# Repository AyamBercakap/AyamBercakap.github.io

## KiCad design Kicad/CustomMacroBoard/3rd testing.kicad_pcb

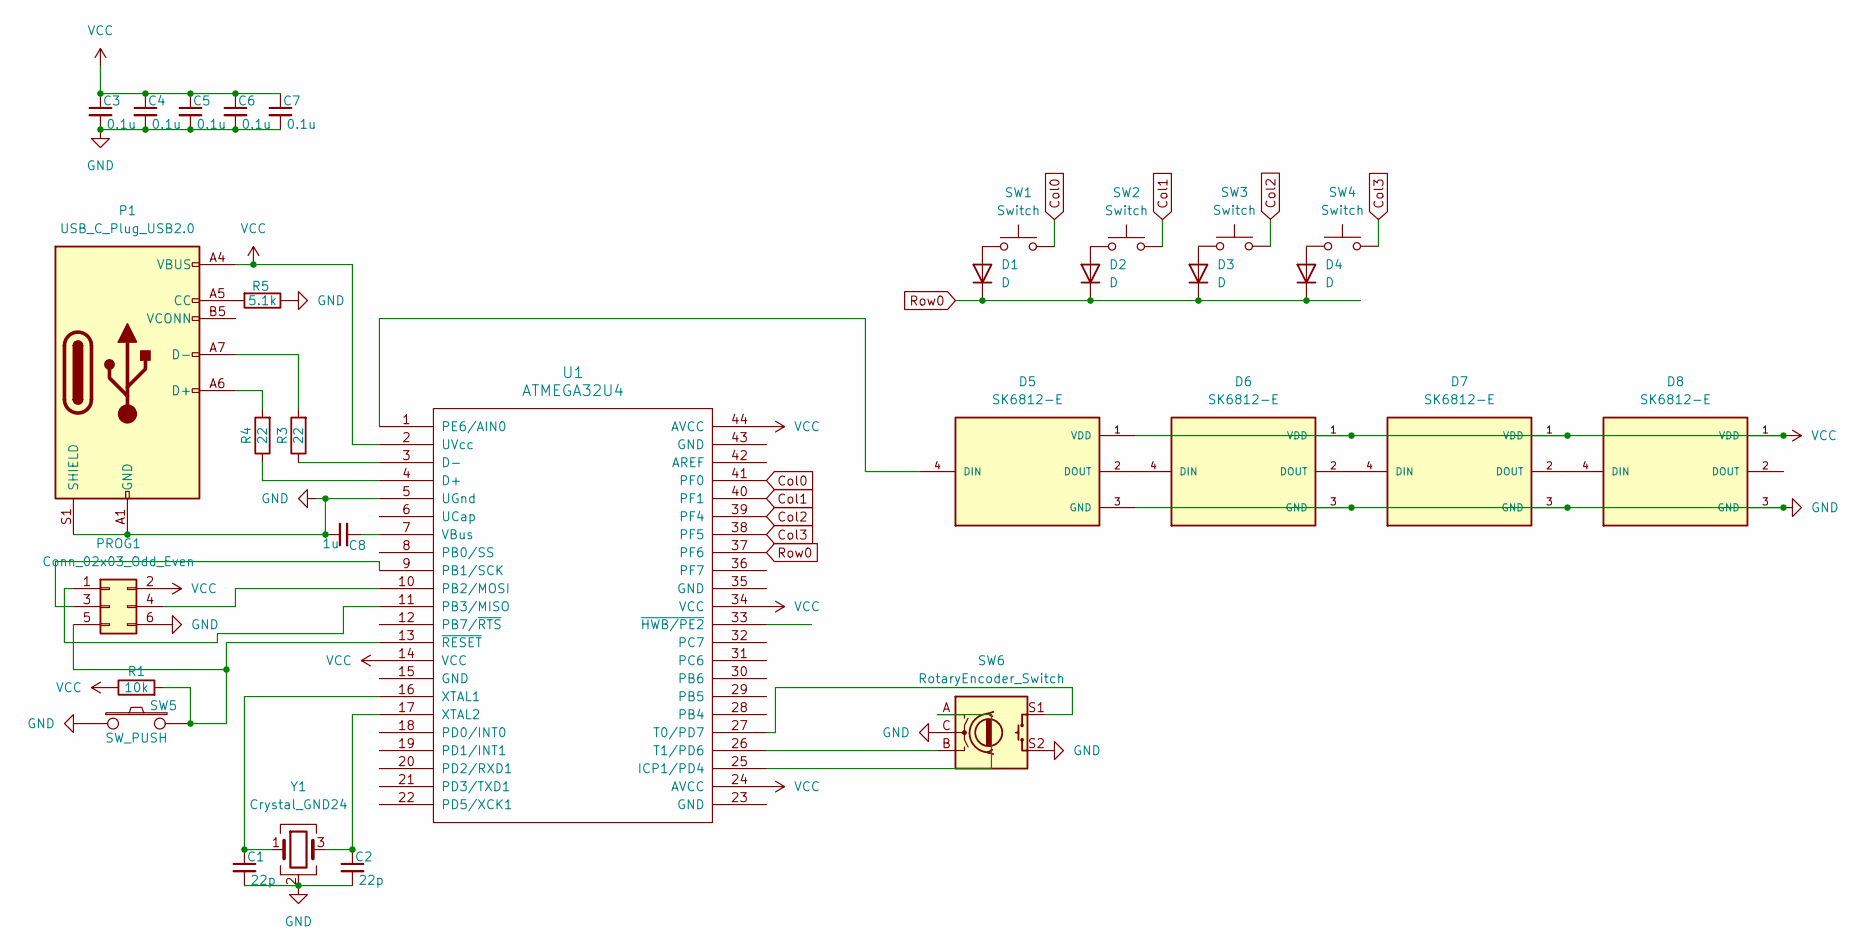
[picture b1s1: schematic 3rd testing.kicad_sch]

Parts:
C1, C2: 22p; C_0805_2012Metric_Pad1.18x1.45mm_HandSolder
C3, C4, C5, C6, C7: 0.1u; C_0805_2012Metric_Pad1.18x1.45mm_HandSolder
C8: 1u; C_0805_2012Metric_Pad1.18x1.45mm_HandSolder
D1, D2, D3, D4: D; D_SOD123_axial
D5, D6, D7, D8: SK6812-E; LED_SK6812-E; PARTREV 2
P1: USB_C_Plug_USB2.0; USB_C_Receptacle_GCT_USB4085
PROG1: Conn_02x03_Odd_Even; pads
R1: 10k; R_0805_2012Metric_Pad1.20x1.40mm_HandSolder
R3, R4: 22; R_0805_2012Metric_Pad1.20x1.40mm_HandSolder
R5: 5.1k; R_0805_2012Metric_Pad1.20x1.40mm_HandSolder
SW1, SW2, SW3, SW4: Switch; MX_PCB_1.00u
SW5: SW_PUSH; SW_SPST_TL3342
SW6: RotaryEncoder_Switch; RotaryEncoder_Alps_EC11E-Switch_Vertical_H20mm
U1: ATMEGA32U4; TQFN-44-1EP_7x7mm_P0.5mm_EP4.7x4.7mm
Y1: Crystal_GND24; Crystal_SMD_SeikoEpson_FA238-4Pin_3.2x2.5mm_HandSoldering

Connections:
Col0: SW1.2, U1.41 (PF0)
Col1: SW2.2, U1.40 (PF1)
Col2: SW3.2, U1.39 (PF4)
Col3: SW4.2, U1.38 (PF5)
GND: C1.2, C2.2, C3.2, C4.2, C5.2, C6.2, C7.2, C8.1, D5.3 (GND), D6.3 (GND), D7.3 (GND), D8.3 (GND), P1.A1 (GND), P1.A12 (GND), P1.B1 (GND), P1.B12 (GND), P1.S1 (SHIELD), PROG1.6, R5.1, SW5.1, SW6.C, SW6.S2, U1.5 (UGnd), Y1.2 (G), Y1.4 (G)
unnamed: D1.2 (A), SW1.1
unnamed: D2.2 (A), SW2.1
unnamed: D3.2 (A), SW3.1
unnamed: D4.2 (A), SW4.1
unnamed: D5.4 (DIN), U1.1 (PE6/AIN0)
unnamed: D5.2 (DOUT), D6.4 (DIN)
unnamed: D6.2 (DOUT), D7.4 (DIN)
unnamed: D7.2 (DOUT), D8.4 (DIN)
unnamed: P1.A5 (CC), R5.2
unnamed: P1.A6 (D+), R4.2
unnamed: P1.A7 (D-), R3.2
unnamed: PROG1.1, U1.11 (PB3/MISO)
unnamed: PROG1.3, U1.9 (PB1/SCK)
unnamed: PROG1.4, U1.10 (PB2/MOSI)
unnamed: PROG1.5, R1.2, SW5.2, U1.13 (~RESET)
unnamed: R4.1, U1.4 (D+)
unnamed: R3.1, U1.3 (D-)
unnamed: SW6.A, U1.25 (ICP1/PD4)
unnamed: SW6.S1, U1.27 (T0/PD7)
unnamed: SW6.B, U1.26 (T1/PD6)
unnamed: C8.2, U1.7 (VBus)
unnamed: C1.1, U1.16 (XTAL1), Y1.1
unnamed: C2.1, U1.17 (XTAL2), Y1.3
Row0: D1.1 (K), D2.1 (K), D3.1 (K), D4.1 (K), U1.37 (PF6)
VCC: C3.1, C4.1, C5.1, C6.1, C7.1, D5.1 (VDD), D6.1 (VDD), D7.1 (VDD), D8.1 (VDD), P1.A4 (VBUS), P1.A9 (VBUS), P1.B4 (VBUS), P1.B9 (VBUS), PROG1.2, R1.1, U1.2 (UVcc), U1.14 (VCC), U1.24 (AVCC), U1.34 (VCC), U1.44 (AVCC)

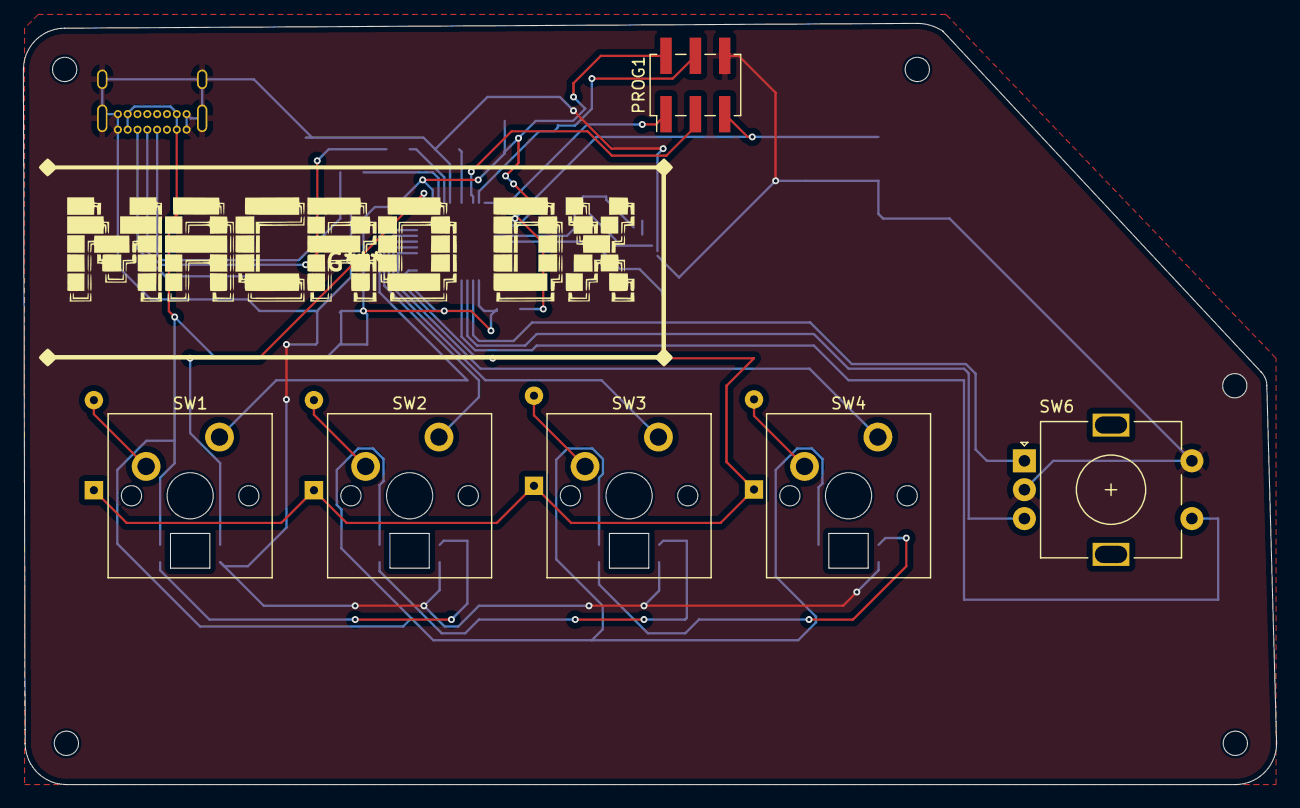
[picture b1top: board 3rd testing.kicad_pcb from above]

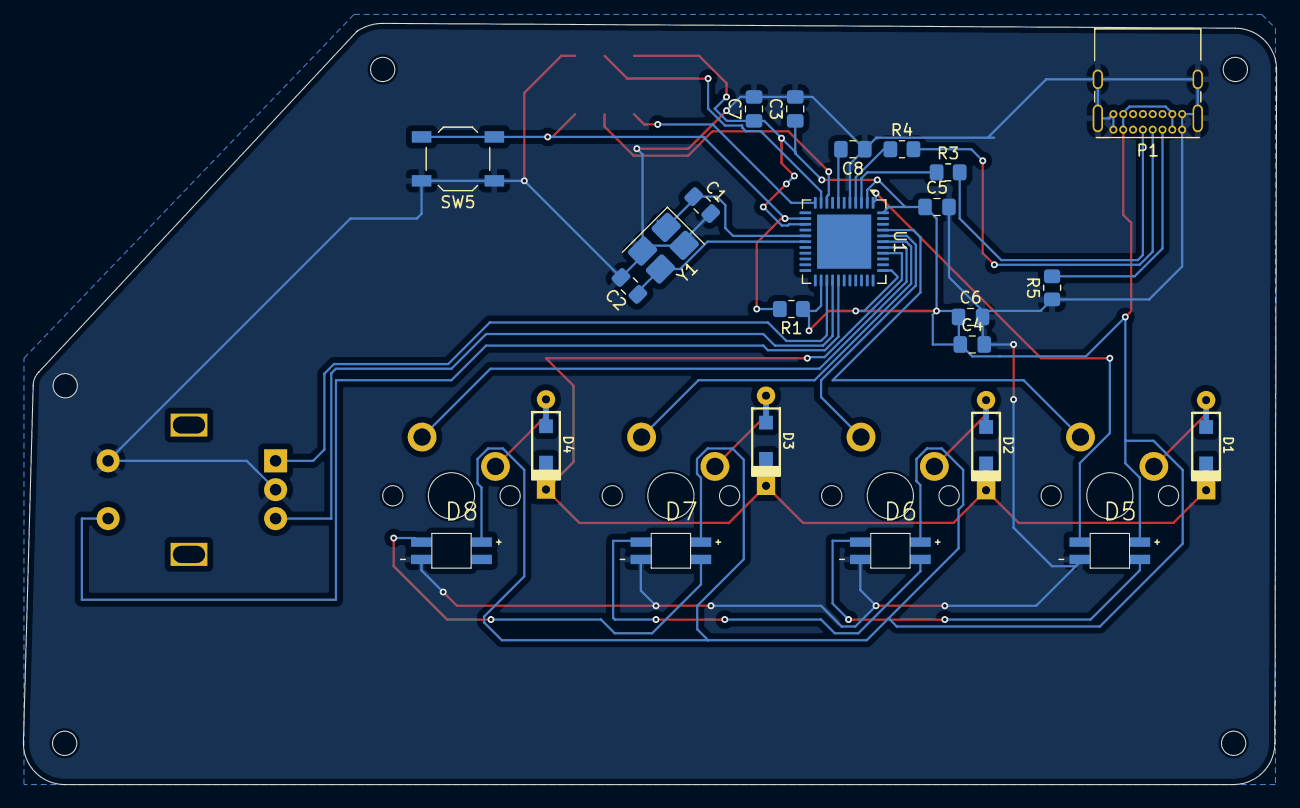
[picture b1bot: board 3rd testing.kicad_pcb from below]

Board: 2 copper layers, 108.5 x 65.9 mm, 30 parts (24 on the bottom side), 30 nets.

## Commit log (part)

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2025-03-24 Scrambler system overhaul
2025-03-24 Redo text-scrambler.js
2025-03-25 Added Continuous scrambling function
2025-03-25 changed default scramble color
2025-03-25 removed previous placeholer comments
2025-03-25 Added folder
2025-03-25 Rename Lab 1 C.html to test
2025-03-25 removed test file
2025-03-25 Tab content system overhaul
2025-03-25 Finishing up with tabcontent
2025-03-25 Setting default tab
2025-03-25 testing again...
2025-03-25 resizing...
2025-03-25 again
2025-03-25 testing custom charset for scrambler
2025-03-25 reverting willfigure out later
2025-03-25 charset now supports global variables
2025-03-25 Testing, will undo later
2025-03-25 forgot to change colors
2025-03-25 testing again
2025-03-25 i swear this is the last change
2025-03-25 Re-added scrambler support in tabs.js
2025-03-25 Re-added tab detection in text-scrambler.js
2025-03-25 added tab scrambler to css
2025-03-25 Added mapping and mapping variable support
2025-03-25 testing mapping and mapping variable function
2025-03-25 Testing with something simpler
2025-03-26 visibility fix for simple tet
2025-03-26 fixing mapping system
2025-03-26 various fixes
2025-03-26 i forgot the damn javascript
2025-03-26 another thing i forgot
2025-03-26 testing
2025-03-26 made mapping not case sensitive
2025-03-26 made scrambler automatically ignore space and &nbsp
2025-03-26 rookie mistake
2025-03-26 fixing ignore space
2025-03-26 i forgot something
2025-03-26 fix variable not detected
2025-03-26 another variable fix
2025-03-26 made attributes clearer
2025-03-26 testing all functions
2025-03-26 Fixed the way text-scrambler handles text based html tag
2025-03-26 Revert "Update text-scrambler.js"
    This reverts commit 4163273e0fd24db280766d0c3f3b70975363b9f5.
2025-03-26 Fixed the way how text-scrambler handles text based html tag
2025-03-26 space now wont scramble by default
    it will only be scrambled if the attribute scrambler-spc was set to true
2025-03-26 testing space scrambler
2025-03-26 fix scramble space screwing the html tags
2025-03-26 fixing again
    why wont it work
    why wont it work
    why wont it work
    why wont it work
    why wont it work
    why wont it work
2025-03-26 test change
2025-03-26 fix scrambling new line
    will still happen when scramble-spc sets to true
2025-03-26 reverted scramble-spc function and added /n to the original scramble-spc function
2025-03-27 fix again
2025-03-27 restoring original homepage
2025-03-27 forgot auto initialization
2025-03-27 implemented new text scrambler system to work with tabs
2025-03-27 changed index.css to acommodate new scrambler system
2025-03-27 FIxed all text scrambling when one tab is activated
2025-03-27 added inactive tab animation controller
2025-03-27 debugging
2025-03-27 removed intialization
    intialization will now be handled by tab.js
2025-03-27 added fallback function
2025-03-27 allows tab.js to fallback when charset or mapping is invalid
2025-03-27 whoops
    forgot to add skip scramble function under setText(newText)
2025-03-27 not sure what's wrong
2025-03-27 just moving random stuff atp
2025-04-07 Removed text-scrambler.js
2025-04-07 Added fixed text-scrambler.js and an extra function font-scrambler.js
2025-04-07 Updated index.css and index.html
2025-04-07 added button support for tabs
2025-04-07 Removed placeholder text
2025-04-07 fixed some whoopsies :)
2025-04-07 added some testing text
2025-04-07 replaced original galactic font to minecraft galactic font
2025-04-08 reverted galactic font
2025-04-19 Create a
2025-04-19 added ump svg
2025-04-19 add bordered version
2025-04-19 Create
2025-04-19 add bw tiles
2025-04-19 Update and rename turquoise straight stripe Tile BG.svg to v
2025-04-19 mistakes were made in the previous one
2025-04-19 why wont they connect T-T
2025-04-19 finalized tile
    i hope illustrator works properly T~T
2025-04-20 grayscale variation of the logo
2025-04-20 pretty obvious from the title
2025-04-20 pfp login icon
2025-06-04 pearto
2025-06-16 testin
2026-02-17 Create filegen
2026-02-17 Add files via upload
    uploaded files
2026-02-23 create new directory
